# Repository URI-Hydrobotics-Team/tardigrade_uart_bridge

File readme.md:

# Tardigrade UART Bridge PCB
A small board that connectes to a host via UART and provides PWM output and GPIO for other boards such as and ESC stack or power management board.

## Techinical Overview
Will be based around the Atmega328p SMD package (which has six configurable PWM outputs). The chip will talk to the host via UART biderctionally. We will flash an arduino bootloader on the MCU for ease of programming.

## Pins
### Main Power Conenctor
- GND
- Power (3.3 - 5v)

### Host Connector
- Serial RX
- Serial TX
- GND

### Power Board Connector
- GND
- V_BATT_MEASURE (analog, voltage divider output for battery voltage)
- 3.3V control
- 5.5V control

### ESC Stack Connector
- GND
- KILL_STATUS (digital, kill switch detection)
- KILL (digital, if kill switch in we can overide it with this)
- PWM_0 - PWM_5 (6x, analog, pwm outputs)

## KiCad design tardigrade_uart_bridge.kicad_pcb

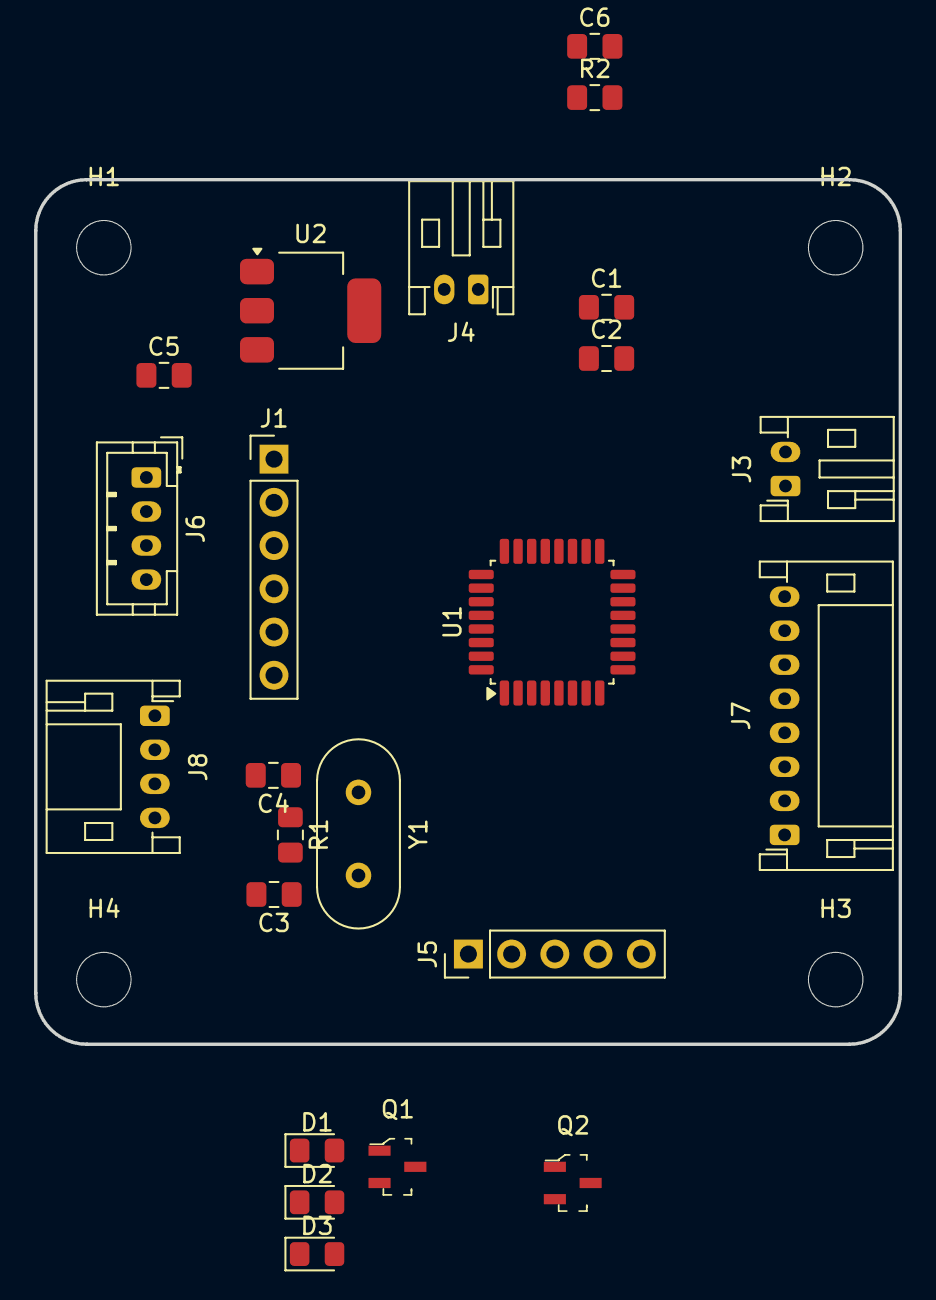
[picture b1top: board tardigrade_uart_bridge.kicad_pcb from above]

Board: 2 copper layers, 50.8 x 50.8 mm, 27 parts (0 on the bottom side), 21 nets, no tracks yet.

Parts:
C1, C2: 100nF; C_0805_2012Metric_Pad1.18x1.45mm_HandSolder
C3, C4: 22pF; C_0805_2012Metric_Pad1.18x1.45mm_HandSolder
C5: 10uF; C_0805_2012Metric_Pad1.18x1.45mm_HandSolder
C6: 22uF; C_0805_2012Metric_Pad1.18x1.45mm_HandSolder
D1, D2: LED_TX; LED_0805_2012Metric_Pad1.15x1.40mm_HandSolder
D3: LED_PWR; LED_0805_2012Metric_Pad1.15x1.40mm_HandSolder
H1, H2, H3, H4: MountingHole; MountingHole_3.2mm_M3
J1: Conn_01x06_Socket; PinHeader_1x06_P2.54mm_Vertical
J3, J4: S2B-PH-K-S; JST_PH_S2B-PH-K_1x02_P2.00mm_Horizontal
J5: Conn_01x05_Socket; PinHeader_1x05_P2.54mm_Vertical
J6: S4B-PH-K-S; JST_PH_B4B-PH-K_1x04_P2.00mm_Vertical
J7: S8B-PH-K-S; JST_PH_S8B-PH-K_1x08_P2.00mm_Horizontal
J8: S4B-PH-K-S; JST_PH_S4B-PH-K_1x04_P2.00mm_Horizontal
Q1, Q2: MMBT2222A-TP; SOT-23-3
R1: 1M; C_0805_2012Metric_Pad1.18x1.45mm_HandSolder
R2: 10k; C_0805_2012Metric_Pad1.18x1.45mm_HandSolder
U1: ATmega328P-A; TQFP-32_7x7mm_P0.8mm
U2: AZ1117H-3.3TRE1; SOT-223-3_TabPin2
Y1: Crystal; Crystal_HC49-U_Vertical

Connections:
3.3V: C1.2, C2.1, J1.6, R2.2, U1.4 (VCC), U1.6 (VCC), U1.18 (AVCC)
/I2C_SCL: J1.3, J6.3, U1.28 (PC5)
/I2C_SDA: J1.2, J6.2, U1.27 (PC4)
/ICSP_MISO: J5.3, J7.6, U1.15 (PB3)
/ICSP_MOSI: J5.2, U1.16 (PB4)
/ICSP_SCK: J5.4, U1.17 (PB5)
/PWM0: J7.2, U1.10 (PD6)
/PWM1: J7.3, U1.9 (PD5)
/PWM2: J7.4, U1.13 (PB1)
/PWM3: J7.5, U1.14 (PB2)
/PWM5: J7.7, U1.1 (PD3)
/UART_HOST_RX: J8.3, Q2.1 (B), U1.31 (PD1)
/UART_HOST_TX: J8.2, Q1.1 (B), U1.30 (PD0)
/V+: C5.1, J3.2, J4.2, J8.4, U2.3 (VI)
/mcu/MCU_RESET: R2.1, U1.29 (~RESET/PC6)
/mcu/XTAL1: C4.1, R1.1, U1.7 (XTAL1/PB6), Y1.1
/mcu/XTAL2: C3.1, R1.2, U1.8 (XTAL2/PB7), Y1.2
GND: C1.1, C2.2, C3.2, C4.2, C5.2, C6.2, D3.1 (K), J1.1, J3.1, J4.1, J5.1, J6.1, J7.1, J8.1, Q1.2 (E), Q2.2 (E), U1.3 (GND), U1.5 (GND), U1.21 (GND), U2.1 (GND)
unnamed: D1.1 (K), Q1.3 (C)
unnamed: D2.1 (K), Q2.3 (C)
unnamed: C6.1, U2.2 (VO)
